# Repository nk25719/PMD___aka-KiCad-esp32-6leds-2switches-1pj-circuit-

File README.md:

# PMD
A "Pseudo Medical Device" and more

## Summary
An ESP32 microcontroller project with a printed cirucit designed by nagham.kheir25.  
This repository contains files which started as a KiCad home work project but which has evolved to become so usefull that in the summer of 2024 orders were placed for real hardware from JLCPCB for delivery in USA and from PCBWay for delivery in Lebanon.  
Begun as Homework 2, by late 2024 we began refering to it as a "Pseudo Medical Device" akd **PMD**.  
At times the PMD approximates the Krake hardware of the Public Invention project Krake. See: https://github.com/PubInv/krake  

## Status 
As of 20240911 See the README.md with in the Firmware folder for descriptions of files there.
As of 202709  
Journal of assembly of PCBWay order in this issue:  https://github.com/nk25719/KiCad-esp32-6leds-2switches-1pj-circuit/issues/33  
Journal of assembly of JLCPCB order in this issue:  https://github.com/nk25719/KiCad-esp32-6leds-2switches-1pj-circuit/issues/32  

To finish the assemblies LEDs were soldered to the PCB 
Image of assembly with LEDs on the Public Inventino GPAD stand off spacers.    

Another view of the LEDs.  

PMD mounted to the workbench

View of the PMD on the workbench. Workbench designed by Oyindamola Adeniran 

Several firmware "sketches" have been developed to assist in the verification of the assemblies including a marching 1 and marching 0 test.

During brain storming we have discussed how this assembly might be used as a "PMD" Pesudo Medical Device. A device to control a Krake and the Mocking Krake. (See Krake: https://github.com/PubInv/krake)

## The KiCad File "HOMEWORK 2" 

The "HOMEWORK 2" PCB is designed around the ESP32 Devkit V1. Documentation for the devkit V1 can be found here.
https://embedded-systems-design.github.io/overview-of-the-esp32-devkit-doit-v1/

Valuable symbols and circuits have been acquired and deposited in this repository for the public use:
* ESP32 symbol and footprint libraries.
* A voltage regulation circuit.
* Switches are linked to the input pins of the ESP32 with pull-up resistors.

## PMD Design Summary

* 4 switches connected to the input pins of the esp32
* 6 leds are connected to the output pins of the Esp32
* the voltage regulator supply the esp32 with a 5 V

## Design Details 
 
* ### Esp32-6leds-2switches-1pj-circuit > Kicanvas live view of current schematic and PCB is found at:  

>> [schematic Link](https://kicanvas.org/?github=https%3A%2F%2Fgithub.com%2Fnk25719%2FKiCad-esp32-6leds-2switches-1pj-circuit%2Fblob%2Fmain%2FhomeWork2.kicad_sch) & [PCB Link](https://kicanvas.org/?github=https%3A%2F%2Fgithub.com%2Fnk25719%2FKiCad-esp32-6leds-2switches-1pj-circuit%2Fblob%2Fmain%2FhomeWork2.kicad_pcb)

* ### Esp32-6leds-2switches-1pj-circuit > KiCad PCB Layers View:

> 3D view of the PCB

> All Layers View

## PMD ESP32 Pin Mapping 

| **GPIO number** 	| **Function as used** 	| **ESP32_DEVKITV1 pin number** 	| **Target device**     	|
|-----------------	|----------------------	|-------------------------------	|-----------------------	|
| 0               	| BOOT                 	| BOOT                          	| NA                    	|
| 2               	| LED_BUILTIN / OUTPUT 	| 27                            	| D4-ONOFF              	|
| 34              	| INPUT ONLY           	| 12                            	| S3-muteFiveMin1       	|
| 35              	| INPUT ONLY           	| 11                            	| S4-SendEmergMessage1  	|
| 39              	| INPUT ONLY           	| 13                            	| S2-RepeatCalculation1 	|
| 36              	| INPUT ONLY           	| 14                            	| S1-morseCodeDanger1   	|
| 23              	| OUTPUT               	| 1                             	| D9-MUTE1              	|
| 15              	| OUTPUT               	| 28                            	| D5-coldFood1          	|
| 4               	| OUTPUT               	| 26                            	| D3-babyCrying1        	|
| 5               	| OUTPUT               	| 23                            	| D8-highBP1            	|
| 18              	| OUTPUT               	| 22                            	| D7-SheildFailure1     	|
| 19              	| OUTPUT               	| 21                            	| D6-lostSock1          	|
| 21              	| SDA                  	| 19                            	| SDA LCD               	|
| 22              	| SCL                  	| 17                            	| SCL LCD               	|
| 17              	| TX2                  	| 24                            	| RX DFPLAYER           	|
| 16              	| RX2                  	| 25                            	| TX DFPLAYER           	|
|                 	|                      	|                               	|                       	|

## Facts

* I understand the function of a decoupling resistor.
* I comprehend the rationale behind including a voltage regulator circuit.
* ESP32 input pins require a pull-up resistor.
* It's necessary to include a power flag next to your GND and Vin connections in the KiCad schematic.
* The ESP32 antenna should be positioned at the edge of the PCB.
* The anular ring between the inner and outer diameters of the through holes in the ESP32 footprint is 0.7 mm.
* the pins of the Esp32 are numberred counter clockwise
* Fun Fact, LED_BUILTIN Not Defined for ESP32 Dev Module but is defined for ESP32S2 Dev Module

## Do Not Tell

* I've made errors.
* Engineers and spelling are not bestfriends.
* I was about to distroy the universe but my ESP32 was not strong enough.

## Did You Know? 

In propositional logic and Boolean algebra, De Morgan's laws, AKA De Morgan's theorem,  
are a pair of transformation rules that are both valid rules of inference.  
The rules allow the expression of conjunctions and disjunctions purely in terms of each other via negation.
Named after Augustus De Morgan, a 19th-century British mathematician.

## Credits
I would like to express my gratitude to the developers and maintainers of several platforms. Firstly, GitHub, for its project management features, issues tracking, and project board, which have consistently proven useful during our usage. Additionally, I extend my thanks to KiCAD for providing the tools necessary for schematic capture and PCB design. I also appreciate the inventors and developers of the Arduino ecosystem, whose tools and hardware have had a profoundly positive impact on many individuals.

Furthermore, I am grateful for the Public Invention platform, which has facilitated communication and collaboration. Special recognition goes to my exceptional mentors and colleague Oyindamola Adeniran, Mr. Forrest Lee Ereckson and Mr. Robert Reed. Their guidance has been invaluable in navigating these projects, fostering skill development, and providing ongoing support. Their mentorship has empowered me to apply my knowledge to projects that benefit public invention.

## License

* Firmware: Affero GPL 3.0
* CERN Open Hardware Licence Version 2 - Strongly Reciprocal

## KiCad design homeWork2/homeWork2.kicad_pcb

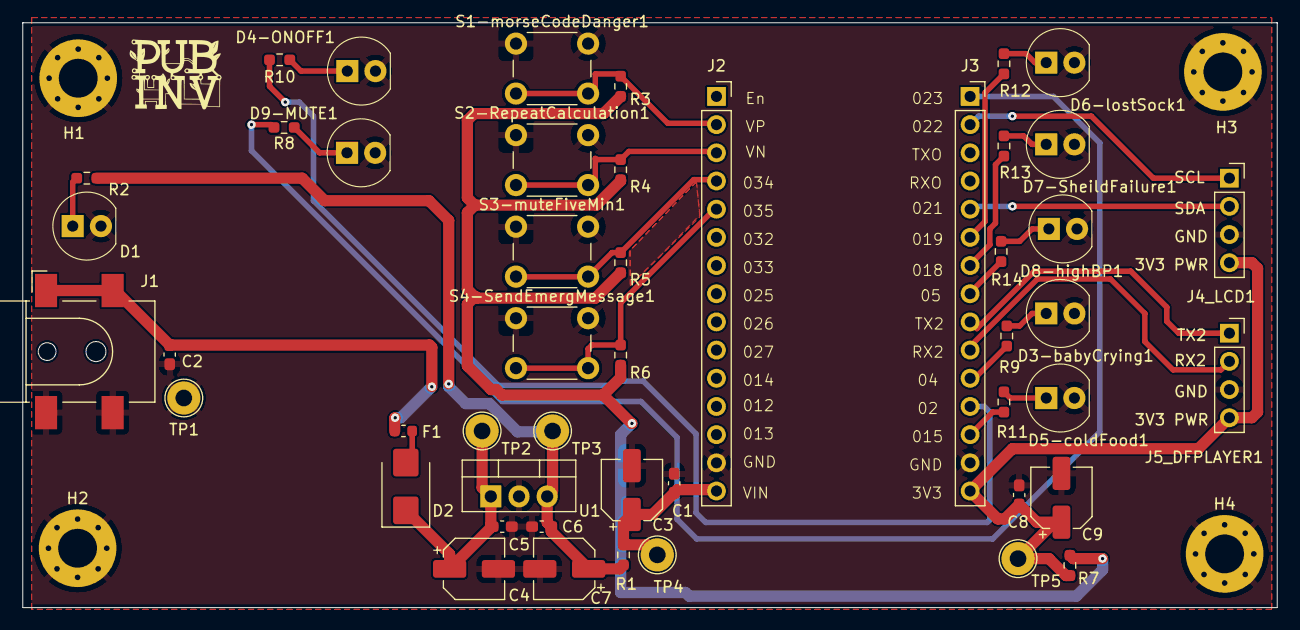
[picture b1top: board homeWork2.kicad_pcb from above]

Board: 2 copper layers, 113.1 x 52.7 mm, 52 parts (0 on the bottom side), 31 nets.

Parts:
C1, C5, C6, C8: 100nF; C_0603_1608Metric_Pad1.08x0.95mm_HandSolder
C2: 39pF; C_0603_1608Metric_Pad1.08x0.95mm_HandSolder
C3, C4, C7, C9: 47uF 16V; CP_Elec_5x5.4
D1, D3-babyCrying1, D4-ONOFF1, D5-coldFood1, D6-lostSock1, D7-SheildFailure1, D8-highBP1, D9-MUTE1: LED_T1.75_CLEAR_RED; LED_5mm_Radial
D2: D_Schottky; D_SMB
F1: Polyfuse_Small; Fuse_0603_1608Metric
H1, H2, H3, H4: MountingHole_Pad_3.5mm; MountingHole_3.5mm_Pad_Via
J1: Barrel_Jack_Switch_SMT; BarrelJack_CLIFF_FC681465S_SMT_Horizontal
J2, J3: Conn_01x15_Socket; PinSocket_1x15_P2.54mm_Vertical
J4_LCD1, J5_DFPLAYER1: Conn_01x04; PinSocket_1x04_P2.54mm_Vertical
R1, R7: 1; R_0603_1608Metric_Pad0.98x0.95mm_HandSolder
R2: 150; R_0603_1608Metric_Pad0.98x0.95mm_HandSolder
R3, R4, R5, R6: 10k; R_0603_1608Metric_Pad0.98x0.95mm_HandSolder
R8, R9, R10, R11, R12, R13, R14: 62; R_0603_1608Metric_Pad0.98x0.95mm_HandSolder
S1-morseCodeDanger1, S2-RepeatCalculation1, S3-muteFiveMin1, S4-SendEmergMessage1: SWITCH_TACTILE_SPST-NO_0.05A_24V; SW_PUSH_6mm_H9.5mm
TP1, TP2, TP3, TP4, TP5: TestPoint; TestPoint_Loop_D2.54mm_Drill1.5mm_Beaded
U1: LM7805_TO220; TO-220-3_Vertical

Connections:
+3.3V: R3.2, R4.1, R5.1, R6.1, R7.2
+5V: C6.1, C7.1, R1.2, R2.2, TP3.1, U1.3 (VO)
/+3V3esp32: C8.1, C9.1, J3.15, J4_LCD1.4, J5_DFPLAYER1.4, R7.1, TP5.1
/+5Vesp32: C1.1, C3.1, J2.15, R1.1, TP4.1
/PVRAW: C2.1, F1.2, J1.1, J1.4
GND: C1.2, C2.2, C3.2, C4.2, C5.2, C6.2, C7.2, C8.2, C9.2, D1.2, D3-babyCrying1.2, D4-ONOFF1.2, D5-coldFood1.2, D6-lostSock1.2, D7-SheildFailure1.2, D8-highBP1.2, D9-MUTE1.2, H1.1, H2.1, H3.1, H4.1, J1.2, J1.3, J2.14, J3.14, J4_LCD1.3, J5_DFPLAYER1.3, S1-morseCodeDanger1.1, S1-morseCodeDanger1.2, S2-RepeatCalculation1.1, S2-RepeatCalculation1.2, S3-muteFiveMin1.1, S3-muteFiveMin1.2, S4-SendEmergMessage1.1, S4-SendEmergMessage1.2, TP1.1, U1.2 (GND)
unnamed: D1.1, R2.1
unnamed: D2.2 (A), F1.1
unnamed: D3-babyCrying1.1, R9.1
unnamed: D4-ONOFF1.1, R10.1
unnamed: D5-coldFood1.1, R11.1
unnamed: D6-lostSock1.1, R12.1
unnamed: D7-SheildFailure1.1, R13.1
unnamed: D8-highBP1.1, R14.1
unnamed: D9-MUTE1.1, R8.1
unnamed: J2.2, R3.1
unnamed: J2.3, R4.2
unnamed: J2.4, R5.2
unnamed: J2.5, R6.2
unnamed: J3.1, R8.2
unnamed: J3.2, J4_LCD1.1
unnamed: J3.5, J4_LCD1.2
unnamed: J3.6, R12.2
unnamed: J3.7, R13.2
unnamed: J3.8, R14.2
unnamed: J3.9, J5_DFPLAYER1.1
unnamed: J3.10, J5_DFPLAYER1.2
unnamed: J3.11, R9.2
unnamed: J3.12, R10.2
unnamed: J3.13, R11.2
Vin: C4.1, C5.1, D2.1 (K), TP2.1, U1.1 (VI)

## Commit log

2024-04-07 Practicing esp32 circuit schematic wiring and PCB routing
    In this homework, I created a symbol for the ESP32 DevKit module and a PCB footprint for it. Additionally, I designed a circuit consisting of 6 lamps, 2 switches, and a power jack. Furthermore, I att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
2024-04-13 Create README.md
    KiCanva link added
2024-04-13 Schematic changes
    the ESP32 symbol library is not saved in the same folder of the project and linked to the footprint library
2024-04-13 Update README.md
    PCB circuit design added
2024-04-13 Update README.md
    More details
2024-04-14 PCB Update
    Copper routing PCB components
2024-04-14 Update README.md
    Image update
2024-04-14 Update README.md
    Additional info and images
2024-04-14 Update README.md
    I made a joke section.
2024-04-20 I added a gitignore file
2024-04-20 this is to clean the deleted backup files and to update the modified pcb file where I attached the copper fill to ground and added text to the silkscreen and to update the sch files where I added the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
2024-04-20 I removed the ground traces and applied copper fill on both the front and back copper layers to establish the ground connections. Additionally, I updated the footprint of the ESP32, positioning the a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
2024-04-21 I updated the ESP32 footprint and symbol, renamed the pins of the ESP32 in a clockwise direction. I rerouted the copper, and ran a DRC test with zero errors and refined the edge cut of the board to m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
2024-04-27 the Barrel Jack is moved to the edge of the board. the copper ainfront of the antenna of the ESP32 is removed, the copper connecting the components to ESP32 is rerouted and routed on the back copper 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
2024-04-27 the coordinates of the PCB changed, the upper corner is set to x=50 y=50. The edgecut measurement is adjusted to integer metric dimension. The mounting holes are also put on well adjusted integer met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
2024-04-28 Four Net Classes are added, default, ground, and two classes for power, one for 5 volts and another for 3.3 volts.The width of the traces used allows 40 degrees Celius temperature rise of the compone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
2024-05-04 Added text box capturing the calculations for setting the currect in LED.
2024-05-04 Functions have been added to the switches and LEDs, and silkscreen has been included on the PCB to indicate these functions.
2024-05-18 Changed the style of routing, the connections are the same.
2024-05-18 library updates
2024-05-21 Added Bill of material and Parts list.
2024-05-22 Update issue templates
2024-05-31 Gerber files and enhancements file are added,
2024-06-02 deleted md file
2024-06-11 updates to the pcb and the schematics.
2024-06-22 capacitors are placed for high frequency and to minimize stray conductance. Classes are editted and a unique Net class is added for power and some net are renamed and assigned to it the suitable Net 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
2024-06-23 Placing the capacitors in a better positions for a better high frequency, and to minimize stray capacitance. And added a label for the power jack net.
2024-06-29 changing net names to better use the net classes. Corrected a short across resistor R1.
2024-06-29 Rerouting +3v3 to the pull up resistors from the bottom layer to the top layer.
2024-07-07 Edited the ESP32 footprint. Rerouted the PCBa and added female socket connectors to the ESP32 and two others to connect an LCD and a DFPLAYER
2024-07-09 PCB and schematics edits. Added a connector for the UART interface and a connection for the I2C interface.
2024-07-09 migrated the library, and updated the symbols in the schematic from the migrated library.
2024-07-09 Cleared the ERC errors.
2024-07-09 Cleared the DRC ERRORS.
2024-07-09 Adding additional JLCPCB partnumbers.
2024-07-10 Updated the parts for available parts manufacturing.
2024-07-13 updating the gerber files to place the pcb order
2024-07-13 adding new gerber files
2024-07-16 Added firmware.
2024-07-16 firmware is added.
2024-07-27 Firmware issue 31
2024-09-01 renamed folder
2024-09-01 adding a mute button, code did not compile
2024-09-01 adding a factory test code to troubleshooting assemblies
2024-09-01 Deleted all the wifi related code and simplified the loop that blinks all the LEDs. fixed the error for the LED connected on pin23, add a semi col.
2024-09-01 remove the DFplayer blocking code. Turned off the LEDs at end of setup. Added serial debug mesages.
2024-09-03 Enhancing the Factory Test Firmware, LED Test issue36
2024-09-04 Edit the factory test marching one and marching zero files to use the millis() method instead of the delay() method
2024-09-04 add switches test firmware
2024-09-07 adding STEP file, incomplete file of the model of the assemblu
2024-09-07 Update README.md
    Update the main README.md with some project status and goal description.
2024-09-08 Remove unused library names in marching firmware. Make a more combined Factory test for WW WZ and Button tests.
2024-09-10 adding the firmware of Krake
2024-09-10 adding LCD factory test code
2024-09-11 Create README.md
    Describe files in the FIRMWARE folder.
2024-09-12 Update README.md
    Mentioned Boards' name
2024-09-12 Update README.md
    Added:
    The "HOMEWORK 2" PCB is designed around the ESP32 Devkit V1. Documentation for the devkit V1 can be found here.
    https://embedded-systems-design.github.io/overview-of-the-esp32-devkit-doit-v1/
2024-09-12 Updates for displaying a Device name, program name, version and date. Working with LCD.
2024-09-12 Move LCD print statements into functions. Give serial port for DFPlayer more descriptive name. Delete dead code. Tested and LCD working in Maryville on USA1 with LCD. WiFi still not working.
2024-09-16 adding factory test arduino ide firware to read the mac address of the esp32 modules
2024-09-28 adding Enclosure design
2024-09-28 Oyin added PCB Board and lenght to one boss. The enclosure looks to be wronged sized.
2024-09-28 Add Holes to PCB
2024-09-28 DF player factory test code
2024-09-28 adding audio files that should go into the sdcard
2024-09-29 Renaming Firmware folder to FactoryTest
2024-10-05 I added blind holes
2024-10-05 Oyin added the PMBWorkbench
2024-10-06 adding pictures of the 3d printed workbench
2024-10-08 testing MQTT
2024-10-12 Update README.md
    adding pictures for the workbench
2024-10-12 Changed boss height, changed color and added a power jack hole.
2024-10-12 Changed color
2024-10-12 Added holes for the translator
2024-10-12 Made bosses longer
2024-10-12 Increased boss height
2024-10-13 Files/flders sorting and more
2024-10-13 fixed file name
2024-10-13 New EnclosureREVb file, no changes made yet
2024-10-13 Added title block to EnclosureREVb
2024-10-15 Change from MQTT_ESP32DevelopmentBoard to FT_PMD_MQTT and bump to version 0.4
2024-10-17 edded the proccessing code
2024-10-18 Make the splash screen conditional with a DEBUG variable on the file FT_PMD_MQTT.
2024-10-19 Adding again the FT_PMD_MQTT.ino and adding Wink.ino
2024-10-19 Oyin made adjustments to the mirror issue and the Enclosure holes
2024-10-19 Modify .gitgnore for FreeCAD back up files.
2024-10-19 Add FreeCAD assemblies for the homework2 board with some ESP32 kits and some screws.
2024-10-19 Changed barrel jack position
2024-10-19 Added PCB Board again
2024-10-19 Added height and width measurements.
2024-10-19 replacing pcb file with a backup file from homeWork2-2024-09-28_140955
2024-10-20 Made the barrel jack hole larger.
2024-10-20 A 3MF file of EnclosureREVb.
2024-10-20 Removed 2D PCB board.
2024-10-22 Update README.md
    Update to the root README.md
    Explain the PMD acronym.
    Add detail to the Summary
    Credit Oyin with the workbench design
2024-10-23 Update README.md
    Adding ESP32 pin mapping
2024-10-24 Update README.md
    Updated the pin map to describe the pin function and add the target device in a new column.
    Updated to the root readme.
2024-10-24 Add GPAD like messages to FT_processingPMD_MQTT.pde and Processing of KrakeModelSerialData and KrakeModelSerialCommands in FT_PMD_MQTT.ino.
2024-10-24 Add additional model serial numbers for USA home work subscriptions on FT_processingPMD_MQTT.pde
2024-10-26 Added ESP32 USB-HOLE, Created a hole for ESP32 model to be accessed from outside the enclosure, increased the depth of the enclosure leaving clearance for the PCBa.
2024-10-27 Updated the switches and added 3d model for the switches.
2024-10-27 adding the footprint folder from GPAD and the parts folder from GPAD to inheret the 3D models of the parts.
2024-10-27 Practicing interrupt and factory testing switch S4
2024-10-27 Refinement of measurements to add allowance between the front panel and the box of the enclosure.
2024-10-27 Adding MQTT factory test sketch
2024-10-27 3mf file for 3D printing the enclosure RevC.
2024-10-27 STEP file for homework2 PCBa.
2024-10-27 Increased the depth of the enclosure and the width of the front panel.
2024-11-02 Moved Enclosure files:: renamed: EnclosureREVb.scad -> Enclosure_and_Workbench/EnclosureREVb.scad, renamed: EnclosureREVc.scad -> Enclosure_and_Workbench/EnclosureREVc.scad.
2024-11-02 Added accessories for the enclosure. A separator for the LEDs and a keycaps for the switch button.
2024-11-02 temperature reading of the internl chip and handeling emergency with MQTT
2024-11-07 Update README.md
    Added a fact
2024-11-21 Hardware work.
2024-11-21 adding LED seperator design
2024-11-21 adding 3.2 screw design
2024-11-22 Adding Serial splash to report prog name, firmware version, date and time of firmware compilation for issue number 46.
2024-11-22 Adding factory test for switch 4 and LED 5, press s4 to blink LED 5 faster, press again to blink at normal rate.
2024-11-22 Adding datasheets folder.
2024-11-24 Add LCD20x4_RotaryEncoder to mount next to LCD.
2024-11-24 File: LCD20x4_RotaryEncoder.FCStd Change thread on nut to M7 fine thread.
2024-11-25 Adding LED module.
2024-11-25 Commiting ahead of merge
2024-11-27 removing more magic numbers
2024-11-30 Made new enclosure for LCD.
2024-11-30 Adding LCG attachment Naghram asked for.
2024-11-30 minor edits.
2024-11-30 Reduced the height of the EnclosureREVc so that the ESP32 dev kit shows off the top front panel. Translated the hole of the power LED. Recentered the hole of the ESP32 dev kit.
2024-11-30 Added a text feature to the top of EnclosureREVc.1.
2024-11-30 Fabricated the switchkeycaps and the LED separator.
2025-02-20 Adding STL file formats.
2025-03-29 Enclosure new revs and new mechanical PMD parts.
2025-03-29 Adding PMD Firmware.
2025-05-09 Adding PMD software codes files.
2025-05-12 Enclosure_and_Workbench/OLED_Enclosure, Mount for the OLED.
2025-05-12 Enclosure_and_Workbench/PMD_Enclosure_RevA1.scad, PMD Enclosure SCAD file, initial commit.
2025-05-12 Enclosure_and_Workbench/homeWork2 , PCB STEP and STL files added and used in the SCAD PMD enclosure design.
2025-05-13 Adding PMD Enclosure files
2025-05-13 adding indention
2025-05-13 adding bezel to PMD via inclusion
2025-05-13 Bezel almost ready for printing
2025-05-13 removing some unneeded defs
2025-05-17 PMD_Enclosure, Edits and increase in the hight of the enclosure.
2025-05-18 PMD_nclosure, finalized VER REVA1.
2025-05-21 PMD_Enclosure, Enhanced Keycaps to not fall out and editted the dimensions of the enclosure.
2025-05-30 Add PulseSensorAmpd_Processing_Visualizer_ESP32 and associated Arduino sketch for hear rate visulization.
2025-06-07 PMD_Enclosure_RevA1.scad, Add echo to report size of Front and Rear panel.
2025-06-09 LCD20x4_RotaryEncoder.FCStd, Modify the rotary encoder nut.
